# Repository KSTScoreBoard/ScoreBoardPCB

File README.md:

# ScoreBoardPCB

## メモ
LEDアノード側のダイオードの足間隔が狭い＆スルーホールが細い

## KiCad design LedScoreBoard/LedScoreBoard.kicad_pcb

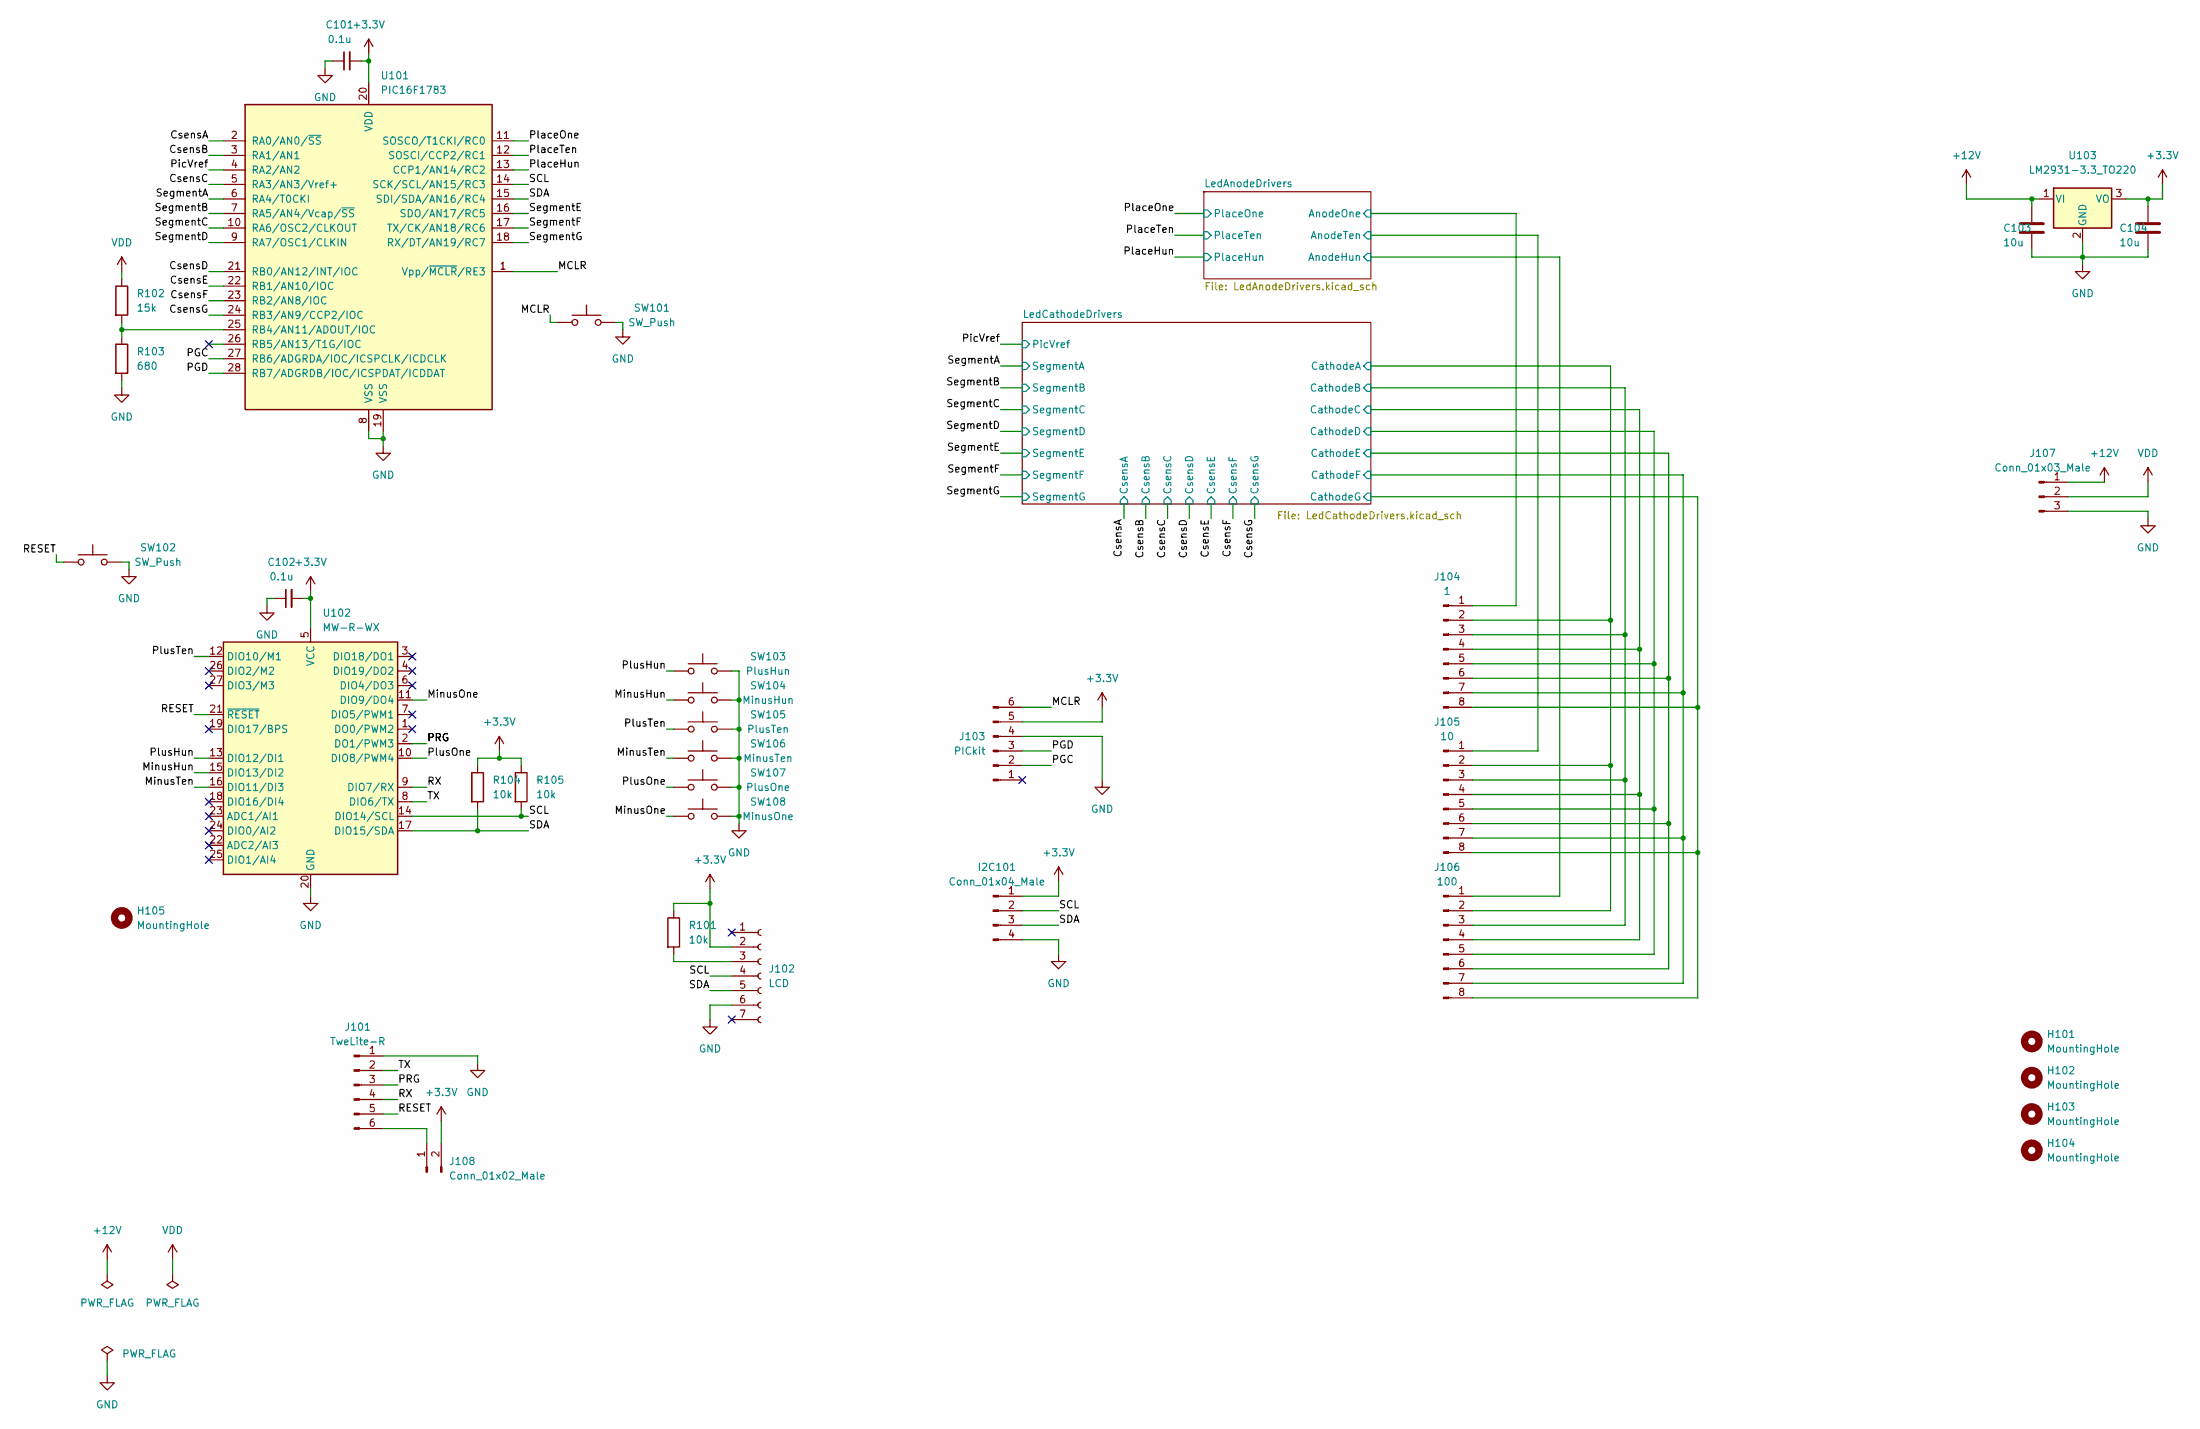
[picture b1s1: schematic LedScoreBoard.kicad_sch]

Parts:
C101, C102: 0.1u; C_0603_1608Metric
C103, C104: 10u; C_0603_1608Metric
H101, H102, H103, H104: MountingHole; MountingHole_3.2mm_M3
H105: MountingHole; MountingHole_6.4mm_M6
I2C101: Conn_01x04_Male; PinHeader_1x04_P2.54mm_Vertical
J101: TweLite-R; PinSocket_1x06_P2.54mm_Horizontal
J102: LCD; PinSocket_1x07_P2.54mm_Vertical
J103: PICkit; PinHeader_1x06_P2.54mm_Horizontal
J104: 1; JST_VH_B8P-VH_1x08_P3.96mm_Vertical
J105: 10; JST_VH_B8P-VH_1x08_P3.96mm_Vertical
J106: 100; JST_VH_B8P-VH_1x08_P3.96mm_Vertical
J107: Conn_01x03_Male; JST_VH_B3P-VH_1x03_P3.96mm_Vertical
J108: Conn_01x02_Male; PinHeader_1x02_P2.54mm_Vertical
R101, R104, R105: 10k; R_0603_1608Metric
R102: 15k; R_0603_1608Metric
R103: 680; R_0603_1608Metric
SW101, SW102: SW_Push; SW_PUSH_6mm
SW103: PlusHun; SW_PUSH_6mm
SW104: MinusHun; SW_PUSH_6mm
SW105: PlusTen; SW_PUSH_6mm
SW106: MinusTen; SW_PUSH_6mm
SW107: PlusOne; SW_PUSH_6mm
SW108: MinusOne; SW_PUSH_6mm
U101: PIC16F1783; DIP-28_W7.62mm_Socket_LongPads
U102: MW-R-WX; MonoWireless_TWE-L-WX
U103: LM2931-3.3_TO220; TO-220-3_Vertical

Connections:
+3.3V: C101.2, C102.2, C104.1, I2C101.1, J102.2, J103.5, J108.2, R101.1, R104.1, R105.1, U101.20 (VDD), U102.5 (VCC), U103.3 (VO)
+12V: C103.1, J107.1, U103.1 (VI); also elsewhere on the board
/CsensA: U101.2 (RA0/AN0/~SS); also elsewhere on the board
/CsensB: U101.3 (RA1/AN1); also elsewhere on the board
/CsensC: U101.5 (RA3/AN3/Vref+); also elsewhere on the board
/CsensD: U101.21 (RB0/AN12/INT/IOC); also elsewhere on the board
/CsensE: U101.22 (RB1/AN10/IOC); also elsewhere on the board
/CsensF: U101.23 (RB2/AN8/IOC); also elsewhere on the board
/CsensG: U101.24 (RB3/AN9/CCP2/IOC); also elsewhere on the board
/LedAnodeDrivers/AnodeHun: J106.1; also elsewhere on the board
/LedAnodeDrivers/AnodeOne: J104.1; also elsewhere on the board
/LedAnodeDrivers/AnodeTen: J105.1; also elsewhere on the board
/LedCathodeDrivers/CathodeA: J104.2, J105.2, J106.2; also elsewhere on the board
/LedCathodeDrivers/CathodeB: J104.3, J105.3, J106.3; also elsewhere on the board
/LedCathodeDrivers/CathodeC: J104.4, J105.4, J106.4; also elsewhere on the board
/LedCathodeDrivers/CathodeD: J104.5, J105.5, J106.5; also elsewhere on the board
/LedCathodeDrivers/CathodeE: J104.6, J105.6, J106.6; also elsewhere on the board
/LedCathodeDrivers/CathodeF: J104.7, J105.7, J106.7; also elsewhere on the board
/LedCathodeDrivers/CathodeG: J104.8, J105.8, J106.8; also elsewhere on the board
/MCLR: J103.6, SW101.1, U101.1 (Vpp/~MCLR/RE3)
/MinusHun: SW104.1, U102.15 (DIO13/DI2)
/MinusOne: SW108.1, U102.11 (DIO9/DO4)
/MinusTen: SW106.1, U102.16 (DIO11/DI3)
/PGC: J103.2, U101.27 (RB6/ADGRDA/IOC/ICSPCLK/ICDCLK)
/PGD: J103.3, U101.28 (RB7/ADGRDB/IOC/ICSPDAT/ICDDAT)
/PRG: J101.3, U102.2 (DO1/PWM3)
/PicVref: U101.4 (RA2/AN2); also elsewhere on the board
/PlaceHun: U101.13 (CCP1/AN14/RC2); also elsewhere on the board
/PlaceOne: U101.11 (SOSCO/T1CKI/RC0); also elsewhere on the board
/PlaceTen: U101.12 (SOSCI/CCP2/RC1); also elsewhere on the board
/PlusHun: SW103.1, U102.13 (DIO12/DI1)
/PlusOne: SW107.1, U102.10 (DIO8/PWM4)
/PlusTen: SW105.1, U102.12 (DIO10/M1)
/RESET: J101.5, SW102.1, U102.21 (~RESET)
/RX: J101.4, U102.9 (DIO7/RX)
/SCL: I2C101.2, J102.4, R105.2, U101.14 (SCK/SCL/AN15/RC3), U102.14 (DIO14/SCL)
/SDA: I2C101.3, J102.5, R104.2, U101.15 (SDI/SDA/AN16/RC4), U102.17 (DIO15/SDA)
/SegmentA: U101.6 (RA4/T0CKI); also elsewhere on the board
/SegmentB: U101.7 (RA5/AN4/Vcap/~SS); also elsewhere on the board
/SegmentC: U101.10 (RA6/OSC2/CLKOUT); also elsewhere on the board
/SegmentD: U101.9 (RA7/OSC1/CLKIN); also elsewhere on the board
/SegmentE: U101.16 (SDO/AN17/RC5); also elsewhere on the board
/SegmentF: U101.17 (TX/CK/AN18/RC6); also elsewhere on the board
/SegmentG: U101.18 (RX/DT/AN19/RC7); also elsewhere on the board
/TX: J101.2, U102.8 (DIO6/TX)
GND: C101.1, C102.1, C103.2, C104.2, I2C101.4, J101.1, J102.6, J103.4, J107.3, R103.2, SW101.2, SW102.2, SW103.2, SW104.2, SW105.2, SW106.2, SW107.2, SW108.2, U101.8 (VSS), U101.19 (VSS), U102.20 (GND), U102.28 (GND), U102.30 (GND), U102.31 (GND), U102.32 (GND), U103.2 (GND); also elsewhere on the board
unnamed: J101.6, J108.1
unnamed: J102.3, R101.2
unnamed: R102.2, R103.1, U101.25 (RB4/AN11/ADOUT/IOC)
VDD: J107.2, R102.1; also elsewhere on the board

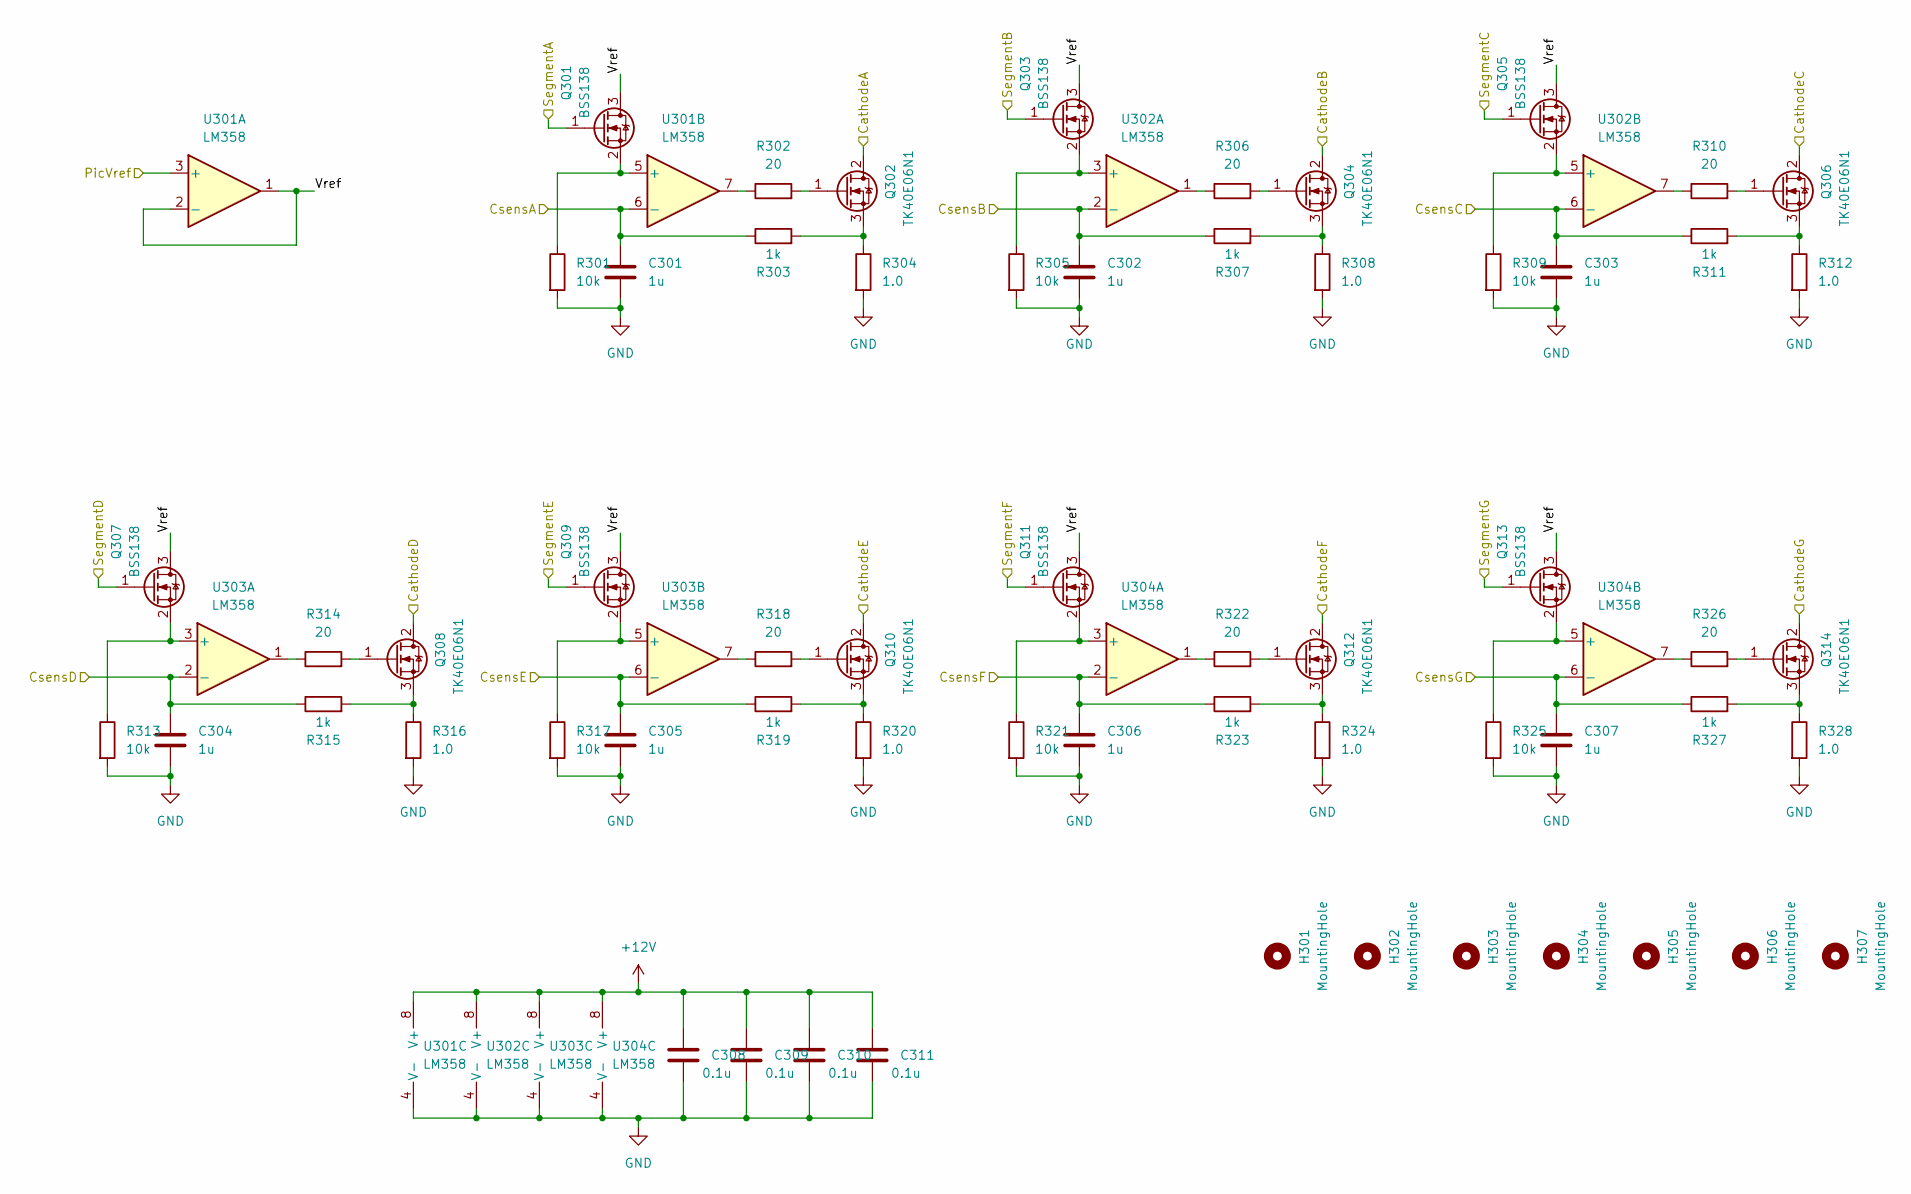
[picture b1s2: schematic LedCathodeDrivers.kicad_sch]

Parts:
C301, C302, C303, C304, C305, C306, C307: 1u; C_0603_1608Metric
C308, C309, C310, C311: 0.1u; C_0603_1608Metric
H301, H302, H303, H304, H305, H306, H307: MountingHole; MountingHole_2.2mm_M2
Q301, Q303, Q305, Q307, Q309, Q311, Q313: BSS138; SOT-23_Handsoldering
Q302, Q304, Q306, Q308, Q310, Q312, Q314: TK40E06N1; TO-220-3_Vertical
R301, R305, R309, R313, R317, R321, R325: 10k; R_0603_1608Metric
R302, R306, R310, R314, R318, R322, R326: 20; R_0603_1608Metric
R303, R307, R311, R315, R319, R323, R327: 1k; R_0603_1608Metric
R304, R308, R312, R316, R320, R324, R328: 1.0; R_2512_6332Metric_Pad1.40x3.35mm_HandSolder
U301, U302, U303, U304: LM358; SOP-8_3.9x4.9mm_P1.27mm

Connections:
+12V: C308.1, C309.1, C310.1, C311.1, U301.8 (V+), U302.8 (V+), U303.8 (V+), U304.8 (V+); also elsewhere on the board
/CsensA: C301.1, R303.1, U301.6 (-); also elsewhere on the board
/CsensB: C302.1, R307.1, U302.2 (-); also elsewhere on the board
/CsensC: C303.1, R311.1, U302.6 (-); also elsewhere on the board
/CsensD: C304.1, R315.1, U303.2 (-); also elsewhere on the board
/CsensE: C305.1, R319.1, U303.6 (-); also elsewhere on the board
/CsensF: C306.1, R323.1, U304.2 (-); also elsewhere on the board
/CsensG: C307.1, R327.1, U304.6 (-); also elsewhere on the board
/LedCathodeDrivers/CathodeA: Q302.2 (D); also elsewhere on the board
/LedCathodeDrivers/CathodeB: Q304.2 (D); also elsewhere on the board
/LedCathodeDrivers/CathodeC: Q306.2 (D); also elsewhere on the board
/LedCathodeDrivers/CathodeD: Q308.2 (D); also elsewhere on the board
/LedCathodeDrivers/CathodeE: Q310.2 (D); also elsewhere on the board
/LedCathodeDrivers/CathodeF: Q312.2 (D); also elsewhere on the board
/LedCathodeDrivers/CathodeG: Q314.2 (D); also elsewhere on the board
/LedCathodeDrivers/Vref: Q301.3 (D), Q303.3 (D), Q305.3 (D), Q307.3 (D), Q309.3 (D), Q311.3 (D), Q313.3 (D), U301.1, U301.2 (-)
/PicVref: U301.3 (+); also elsewhere on the board
/SegmentA: Q301.1 (G); also elsewhere on the board
/SegmentB: Q303.1 (G); also elsewhere on the board
/SegmentC: Q305.1 (G); also elsewhere on the board
/SegmentD: Q307.1 (G); also elsewhere on the board
/SegmentE: Q309.1 (G); also elsewhere on the board
/SegmentF: Q311.1 (G); also elsewhere on the board
/SegmentG: Q313.1 (G); also elsewhere on the board
GND: C301.2, C302.2, C303.2, C304.2, C305.2, C306.2, C307.2, C308.2, C309.2, C310.2, C311.2, R301.2, R304.2, R305.2, R308.2, R309.2, R312.2, R313.2, R316.2, R317.2, R320.2, R321.2, R324.2, R325.2, R328.2, U301.4 (V-), U302.4 (V-), U303.4 (V-), U304.4 (V-); also elsewhere on the board
unnamed: Q301.2 (S), R301.1, U301.5 (+)
unnamed: Q302.1 (G), R302.2
unnamed: Q302.3 (S), R303.2, R304.1
unnamed: Q303.2 (S), R305.1, U302.3 (+)
unnamed: Q304.1 (G), R306.2
unnamed: Q304.3 (S), R307.2, R308.1
unnamed: Q305.2 (S), R309.1, U302.5 (+)
unnamed: Q306.1 (G), R310.2
unnamed: Q306.3 (S), R311.2, R312.1
unnamed: Q307.2 (S), R313.1, U303.3 (+)
unnamed: Q308.1 (G), R314.2
unnamed: Q308.3 (S), R315.2, R316.1
unnamed: Q309.2 (S), R317.1, U303.5 (+)
unnamed: Q310.1 (G), R318.2
unnamed: Q310.3 (S), R319.2, R320.1
unnamed: Q311.2 (S), R321.1, U304.3 (+)
unnamed: Q312.1 (G), R322.2
unnamed: Q312.3 (S), R323.2, R324.1
unnamed: Q313.2 (S), R325.1, U304.5 (+)
unnamed: Q314.1 (G), R326.2
unnamed: Q314.3 (S), R327.2, R328.1
unnamed: R302.1, U301.7
unnamed: R306.1, U302.1
unnamed: R310.1, U302.7
unnamed: R314.1, U303.1
unnamed: R318.1, U303.7
unnamed: R322.1, U304.1
unnamed: R326.1, U304.7

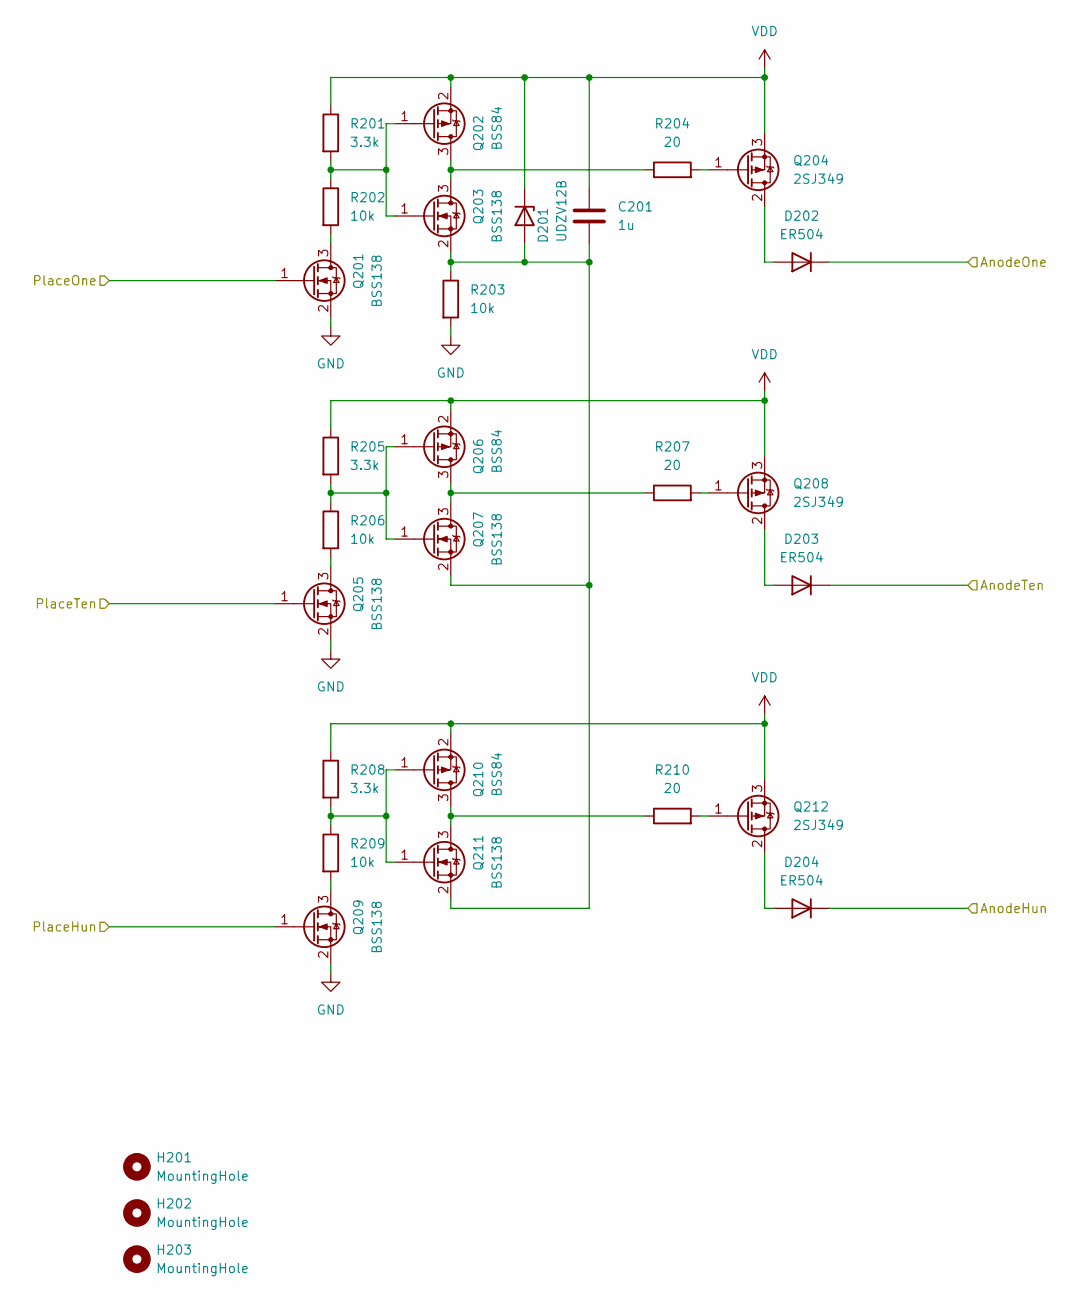
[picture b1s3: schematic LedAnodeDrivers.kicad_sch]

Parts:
C201: 1u; C_0603_1608Metric
D201: UDZV12B; D_TUMD2
D202, D203, D204: ER504; D_DO-27_P15.24mm_Horizontal
H201, H202, H203: MountingHole; MountingHole_2.2mm_M2
Q201, Q203, Q205, Q207, Q209, Q211: BSS138; SOT-23_Handsoldering
Q202, Q206, Q210: BSS84; SOT-23_Handsoldering
Q204, Q208, Q212: 2SJ349; TO-220-3_Vertical
R201, R205, R208: 3.3k; R_0603_1608Metric
R202, R203, R206, R209: 10k; R_0603_1608Metric
R204, R207, R210: 20; R_0603_1608Metric

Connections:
/LedAnodeDrivers/AnodeHun: D204.1 (K); also elsewhere on the board
/LedAnodeDrivers/AnodeOne: D202.1 (K); also elsewhere on the board
/LedAnodeDrivers/AnodeTen: D203.1 (K); also elsewhere on the board
/PlaceHun: Q209.1 (G); also elsewhere on the board
/PlaceOne: Q201.1 (G); also elsewhere on the board
/PlaceTen: Q205.1 (G); also elsewhere on the board
GND: Q201.2 (S), Q205.2 (S), Q209.2 (S), R203.2; also elsewhere on the board
unnamed: C201.2, D201.2 (A), Q203.2 (S), Q207.2 (S), Q211.2 (S), R203.1
unnamed: D202.2 (A), Q204.2 (D)
unnamed: D203.2 (A), Q208.2 (D)
unnamed: D204.2 (A), Q212.2 (D)
unnamed: Q201.3 (D), R202.2
unnamed: Q202.1 (G), Q203.1 (G), R201.2, R202.1
unnamed: Q202.3 (D), Q203.3 (D), R204.1
unnamed: Q204.1 (G), R204.2
unnamed: Q205.3 (D), R206.2
unnamed: Q206.1 (G), Q207.1 (G), R205.2, R206.1
unnamed: Q206.3 (D), Q207.3 (D), R207.1
unnamed: Q208.1 (G), R207.2
unnamed: Q209.3 (D), R209.2
unnamed: Q210.1 (G), Q211.1 (G), R208.2, R209.1
unnamed: Q210.3 (D), Q211.3 (D), R210.1
unnamed: Q212.1 (G), R210.2
VDD: C201.1, D201.1 (K), Q202.2 (S), Q204.3 (S), Q206.2 (S), Q208.3 (S), Q210.2 (S), Q212.3 (S), R201.1, R205.1, R208.1; also elsewhere on the board

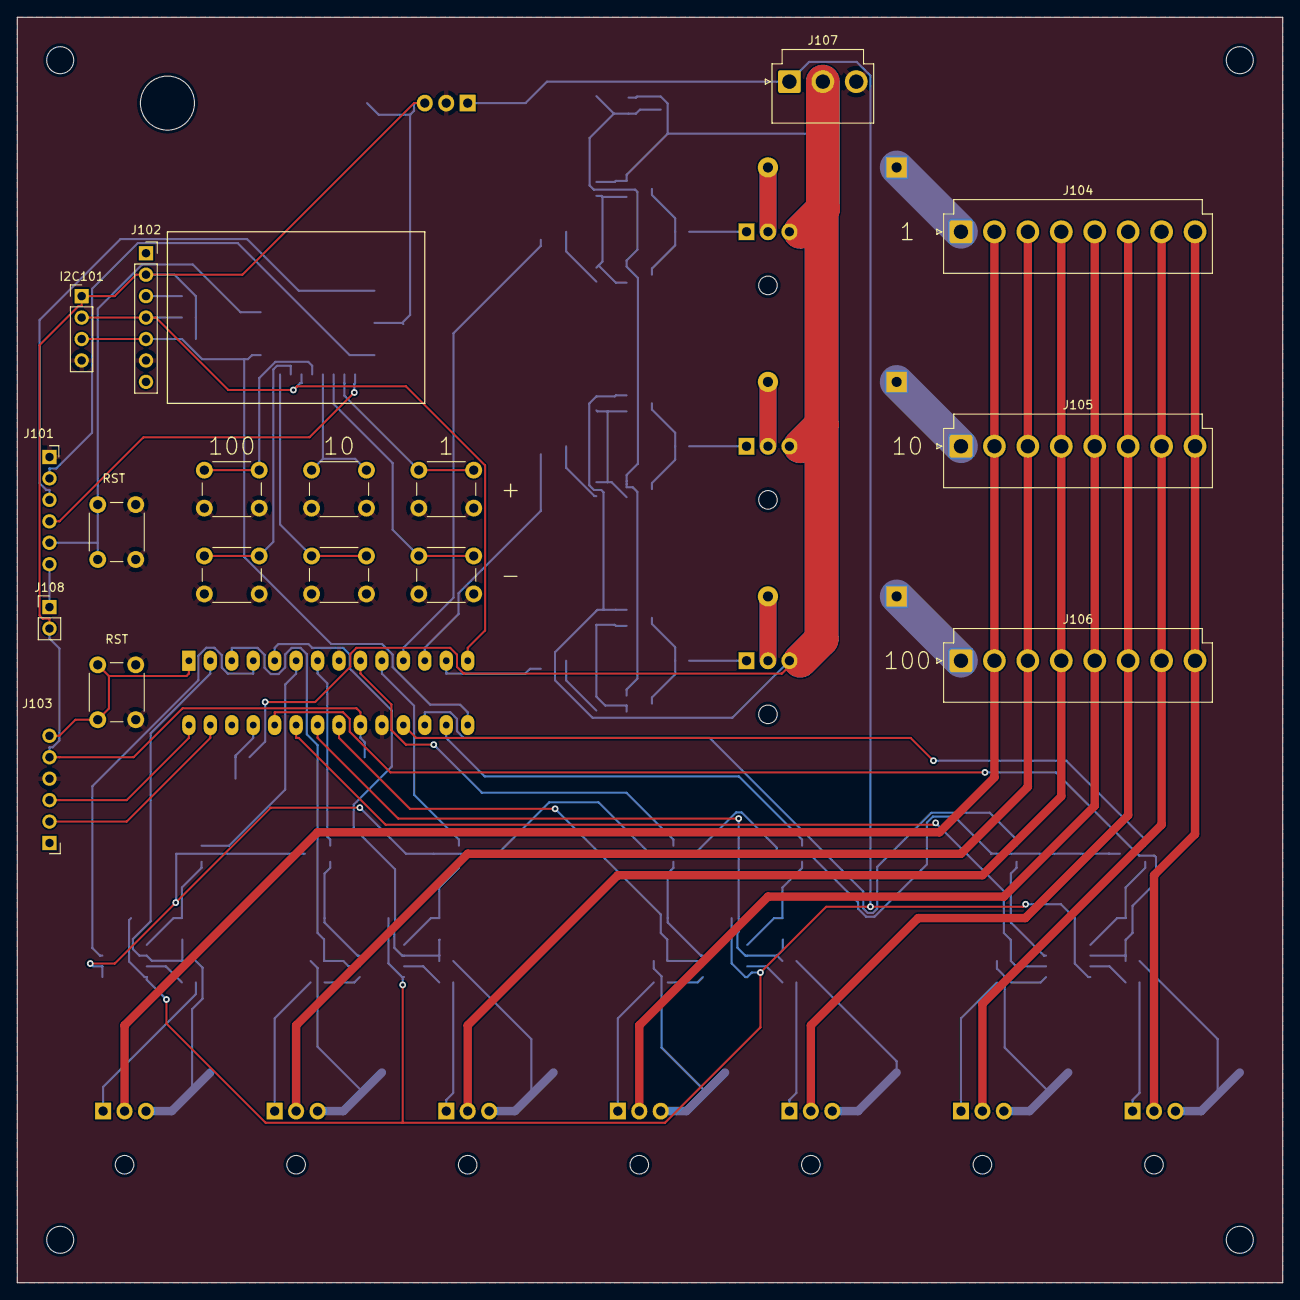
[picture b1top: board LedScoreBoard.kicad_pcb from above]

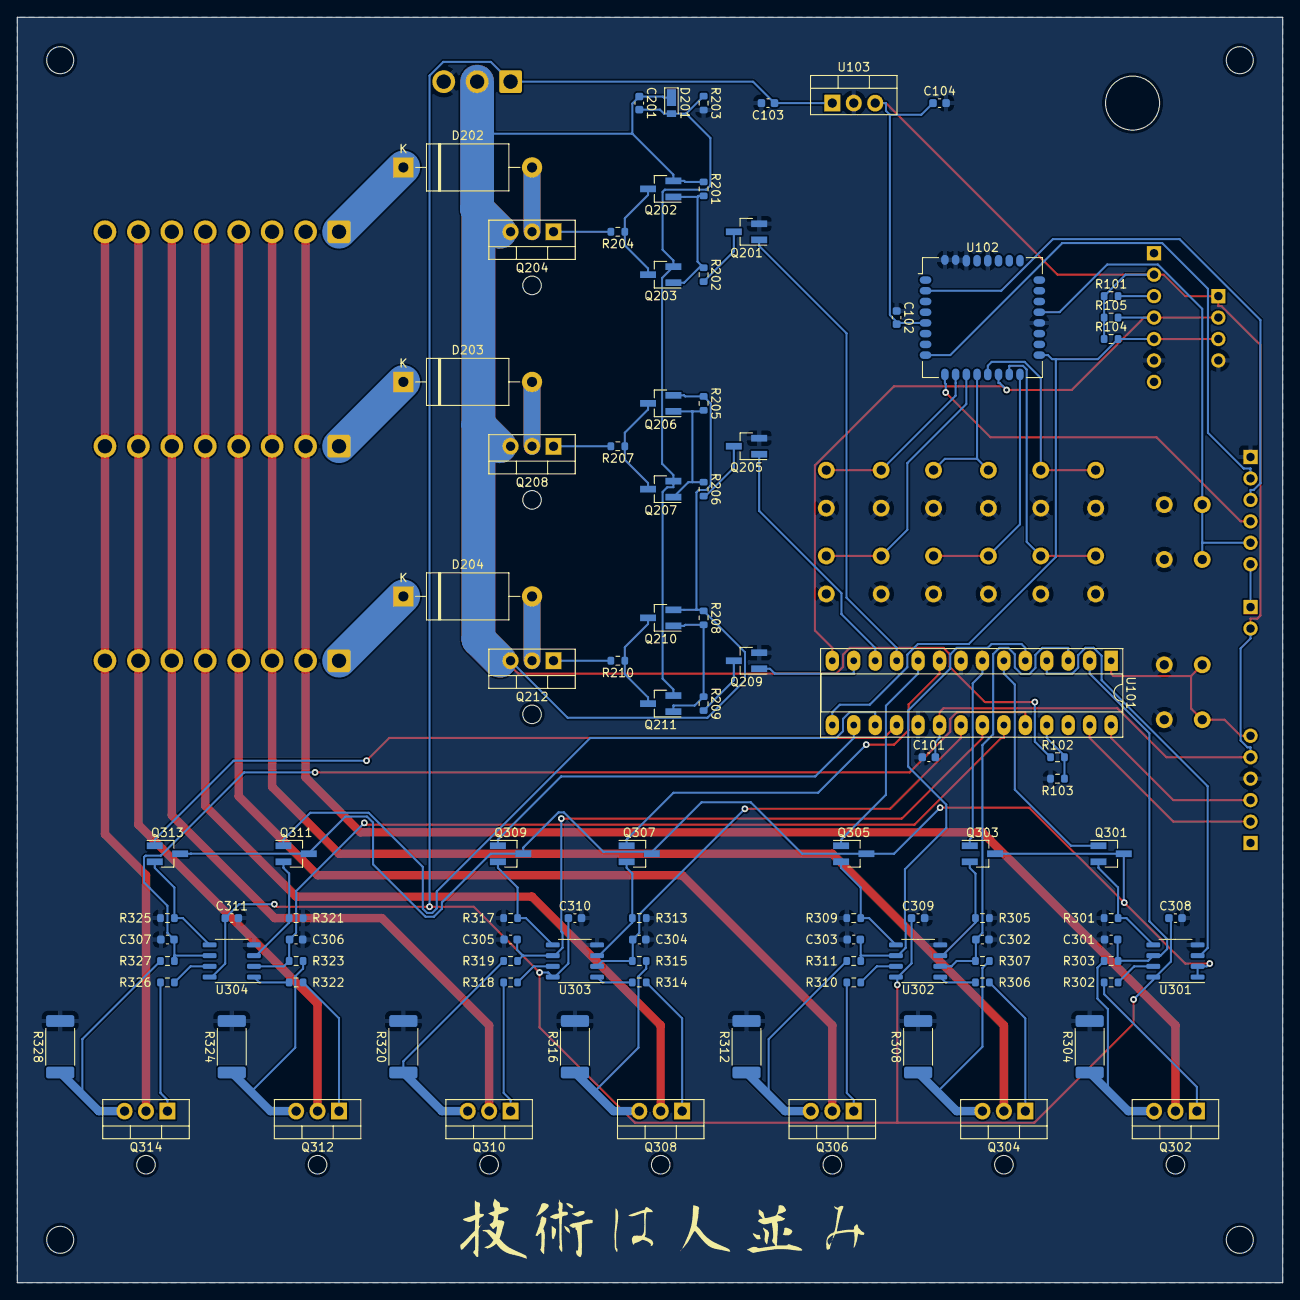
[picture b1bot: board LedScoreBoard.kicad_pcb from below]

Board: 2 copper layers, 149.9 x 149.9 mm, 128 parts (96 on the bottom side), 95 nets.

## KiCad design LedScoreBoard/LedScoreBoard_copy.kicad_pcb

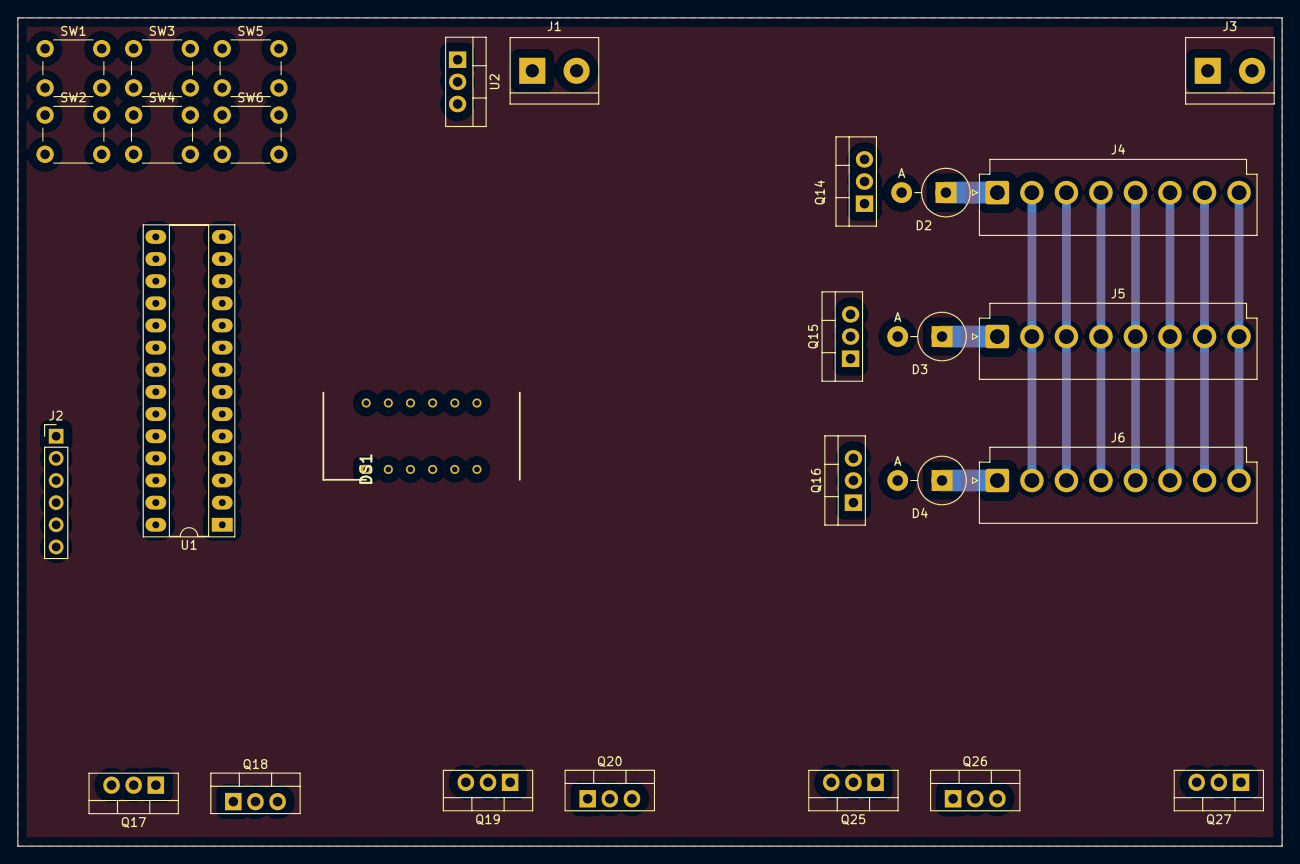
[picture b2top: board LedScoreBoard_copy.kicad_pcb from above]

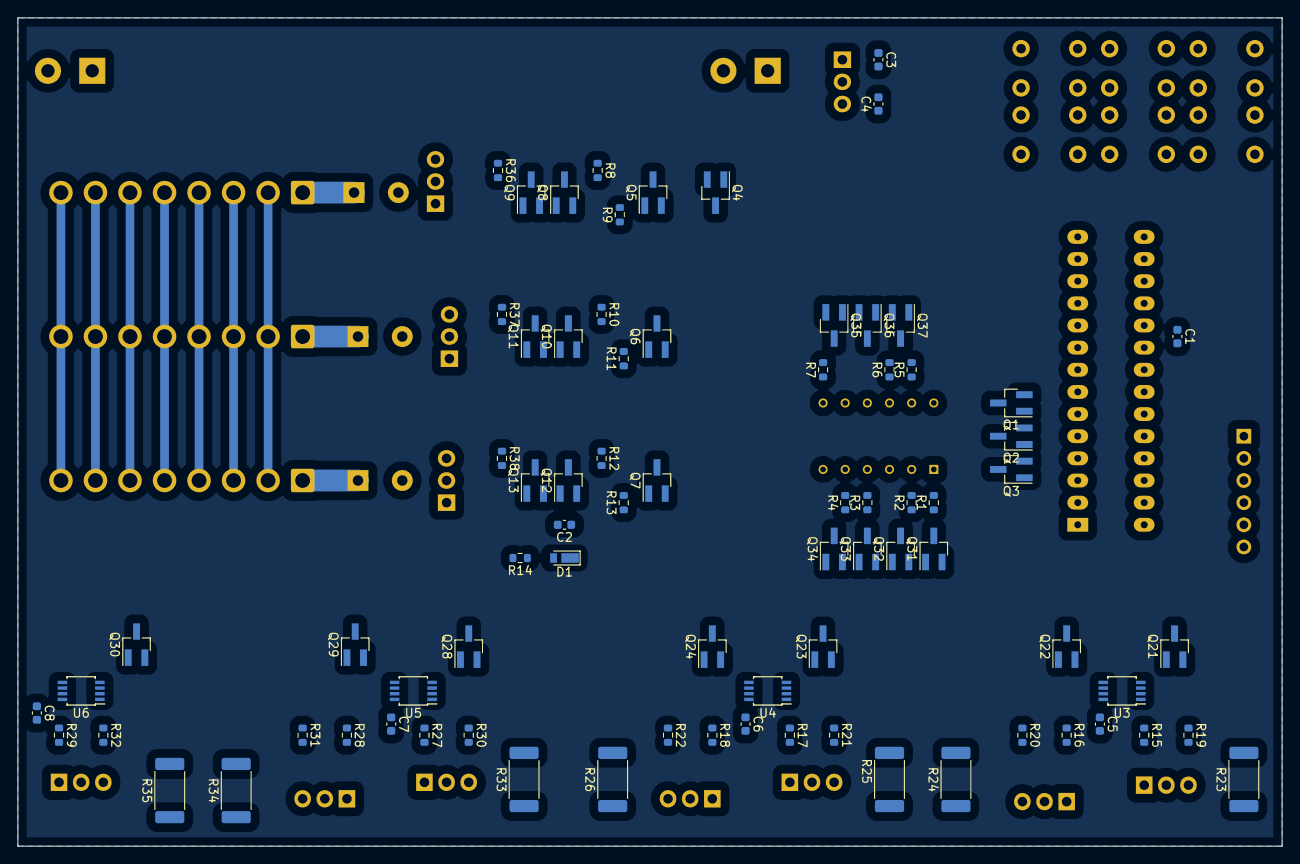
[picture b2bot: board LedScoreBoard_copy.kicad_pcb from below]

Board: 2 copper layers, 145.0 x 95.0 mm, 106 parts (78 on the bottom side), 104 nets.

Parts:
C1, C5, C6, C7, C8: 0.1u; C_0603_1608Metric
C2: 1u; C_0603_1608Metric
C3, C4: 10u; C_0603_1608Metric
D1: GDZJ112C; D_TUMD2
D2, D3, D4: ER504; D_DO-27_P5.08mm_Vertical_AnodeUp
DS1: 2831BS-RIGHT-ANGLE; DIPS762W45P254L2253H610Q12N
J1, J3: Conn_01x02_Male; TerminalBlock_bornier-2_P5.08mm
J2: Conn_01x06_Male; PinHeader_1x06_P2.54mm_Vertical
J4, J5, J6: Conn_01x08_Male; JST_VH_B8P-VH_1x08_P3.96mm_Vertical
Q1, Q2, Q3, Q8, Q10, Q12: BSS84; SOT-23_Handsoldering
Q4, Q5, Q6, Q7, Q9, Q11, Q13, Q21, Q22, Q23, Q24, Q28, Q29, Q30, Q31, Q32, Q33, Q34, Q35, Q36, Q37: BSS138; SOT-23_Handsoldering
Q14, Q15, Q16: 2SJ349; TO-220-3_Vertical
Q17, Q18, Q19, Q20, Q25, Q26, Q27: TK40E06N1; TO-220-3_Vertical
R1, R2, R3, R4, R5, R6, R7, R19, R20, R21, R22, R30, R31, R32: 1k; R_0603_1608Metric
R8, R10, R12: 3.3k; R_0603_1608Metric
R9, R11, R13, R14: 10k; R_0603_1608Metric
R15, R16, R17, R18, R27, R28, R29, R36, R37, R38: 20; R_0603_1608Metric
R23, R24, R25, R26, R33, R34, R35: 1.0; R_2512_6332Metric_Pad1.40x3.35mm_HandSolder
SW1, SW2, SW3, SW4, SW5, SW6: SW_Push; SW_PUSH_6mm
U1: PIC16F1516-ISP; DIP-28_W7.62mm_Socket_LongPads
U2: LM2931-3.3_TO220; TO-220-3_Vertical
U3, U4, U5, U6: LM358; TSSOP-8_3x3mm_P0.65mm

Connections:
+3.3V: C1.2, C4.1, J2.2, Q1.2 (S), Q2.2 (S), Q3.2 (S), U1.20 (VDD), U2.3 (VO)
+12V: C3.1, C5.1, C6.1, C7.1, C8.1, J1.1, U2.1 (VI), U3.8 (V+), U4.8 (V+), U5.8 (V+), U6.8 (V+)
/MCLR: J2.1, U1.1 (Vpp/~MCLR/RE3)
/PGC: J2.5, U1.28 (RB7/ADGRDB/IOC/ICSPDAT/ICDDAT)
/PGD: J2.4, U1.27 (RB6/ADGRDA/IOC/ICSPCLK/ICDCLK)
/Vref: Q21.3 (D), Q22.3 (D), Q23.3 (D), Q24.3 (D), Q28.3 (D), Q29.3 (D), Q30.3 (D)
/anodeHun: D4.1 (K), J6.1
/anodeOne: D2.1 (K), J4.1
/anodeTen: D3.1 (K), J5.1
/cathodeA: J4.2, J5.2, J6.2, Q17.2 (D)
/cathodeB: J4.3, J5.3, J6.3, Q18.2 (D)
/cathodeC: J4.4, J5.4, J6.4, Q19.2 (D)
/cathodeD: J4.5, J5.5, J6.5, Q20.2 (D)
/cathodeE: J4.6, J5.6, J6.6, Q25.2 (D)
/cathodeF: J4.7, J5.7, J6.7, Q26.2 (D)
/cathodeG: J4.8, J5.8, J6.8, Q27.2 (D)
/enable: Q4.1 (G), U1.9 (RA7/OSC1/CLKIN)
/minusHun: SW2.1, U1.26 (RB5/AN13/T1G/IOC)
/minusOne: SW6.1, U1.22 (RB1/AN10/IOC)
/minusTen: SW4.1, U1.24 (RB3/AN9/CCP2/IOC)
/placeHun: Q1.1 (G), Q7.1 (G), U1.13 (CCP1/AN14/RC2)
/placeOne: Q3.1 (G), Q5.1 (G), U1.11 (SOSCO/T1CKI/RC0)
/placeTen: Q2.1 (G), Q6.1 (G), U1.12 (SOSCI/CCP2/RC1)
/plusHun: SW1.1, U1.25 (RB4/AN11/ADOUT/IOC)
/plusOne: SW5.1, U1.21 (RB0/AN12/INT/IOC)
/plusTen: SW3.1, U1.23 (RB2/AN8/IOC)
/segmentA: Q21.1 (G), Q24.1 (G), Q37.1 (G), U1.2 (RA0/AN0/~SS)
/segmentB: Q22.1 (G), Q35.1 (G), U1.3 (RA1/AN1)
/segmentC: Q33.1 (G), U1.4 (RA2/AN2)
/segmentD: Q23.1 (G), Q32.1 (G), U1.5 (RA3/AN3/Vref+)
/segmentE: Q28.1 (G), Q31.1 (G), U1.6 (RA4/T0CKI)
/segmentF: Q29.1 (G), Q36.1 (G), U1.7 (RA5/AN4/Vcap/~SS)
/segmentG: Q30.1 (G), Q34.1 (G), U1.10 (RA6/OSC2/CLKOUT)
GND: C1.1, C3.2, C4.2, C5.2, C6.2, C7.2, C8.2, J1.2, J2.3, J3.2, Q4.2 (S), Q31.2 (S), Q32.2 (S), Q33.2 (S), Q34.2 (S), Q35.2 (S), Q36.2 (S), Q37.2 (S), R14.2, R23.2, R24.2, R25.2, R26.2, R33.2, R34.2, R35.2, SW1.2, SW2.2, SW3.2, SW4.2, SW5.2, SW6.2, U1.8 (VSS), U1.19 (VSS), U2.2 (GND), U3.4 (V-), U4.4 (V-), U5.4 (V-), U6.4 (V-)
unnamed: C2.2, D1.2 (A), Q9.2 (S), Q11.2 (S), Q13.2 (S), R14.1
unnamed: D2.2 (A), Q14.2 (D)
unnamed: D3.2 (A), Q15.2 (D)
unnamed: D4.2 (A), Q16.2 (D)
unnamed: DS1.1 (CATHODE_E), R1.2
unnamed: DS1.2 (CATHODE_D), R2.2
unnamed: DS1.4 (CATHODE_C), R3.2
unnamed: DS1.5 (CATHODE_G), R4.2
unnamed: DS1.7 (CATHODE_B), R7.1
unnamed: DS1.8 (COMMON_ANODE_DIG_3), Q3.3 (D)
unnamed: DS1.9 (COMMON_ANODE_DIG_2), Q2.3 (D)
unnamed: DS1.10 (CATHODE_F), R6.1
unnamed: DS1.11 (CATHODE_A), R5.1
unnamed: DS1.12 (COMMON_ANODE_DIG_1), Q1.3 (D)
unnamed: Q4.3 (D), Q5.2 (S), Q6.2 (S), Q7.2 (S)
unnamed: Q5.3 (D), R9.2
unnamed: Q6.3 (D), R11.2
unnamed: Q7.3 (D), R13.2
unnamed: Q8.1 (G), Q9.1 (G), R8.2, R9.1
unnamed: Q8.3 (D), Q9.3 (D), R36.1
unnamed: Q10.1 (G), Q11.1 (G), R10.2, R11.1
unnamed: Q10.3 (D), Q11.3 (D), R37.1
unnamed: Q12.1 (G), Q13.1 (G), R12.2, R13.1
unnamed: Q12.3 (D), Q13.3 (D), R38.1
unnamed: Q14.1 (G), R36.2
unnamed: Q15.1 (G), R37.2
unnamed: Q16.1 (G), R38.2
unnamed: Q17.1 (G), R15.2
unnamed: Q17.3 (S), R19.2, R23.1
unnamed: Q18.1 (G), R16.2
unnamed: Q18.3 (S), R20.2, R24.1
unnamed: Q19.1 (G), R17.2
unnamed: Q19.3 (S), R21.2, R25.1
unnamed: Q20.1 (G), R18.2
unnamed: Q20.3 (S), R22.2, R26.1
unnamed: Q21.2 (S), U3.3 (+)
unnamed: Q22.2 (S), U3.5 (+)
unnamed: Q23.2 (S), U4.3 (+)
unnamed: Q24.2 (S), U4.5 (+)
unnamed: Q25.1 (G), R27.2
unnamed: Q25.3 (S), R30.2, R33.1
unnamed: Q26.1 (G), R28.2
unnamed: Q26.3 (S), R31.2, R34.1
unnamed: Q27.1 (G), R29.2
unnamed: Q27.3 (S), R32.2, R35.1
unnamed: Q28.2 (S), U5.3 (+)
unnamed: Q29.2 (S), U5.5 (+)
unnamed: Q30.2 (S), U6.3 (+)
unnamed: Q31.3 (D), R1.1
unnamed: Q32.3 (D), R2.1
unnamed: Q33.3 (D), R3.1
unnamed: Q34.3 (D), R4.1
unnamed: Q35.3 (D), R7.2
unnamed: Q36.3 (D), R6.2
unnamed: Q37.3 (D), R5.2
unnamed: R15.1, U3.1
unnamed: R16.1, U3.7
unnamed: R17.1, U4.1
unnamed: R18.1, U4.7
unnamed: R19.1, U3.2 (-)
unnamed: R20.1, U3.6 (-)
unnamed: R21.1, U4.2 (-)
unnamed: R22.1, U4.6 (-)
unnamed: R27.1, U5.1
unnamed: R28.1, U5.7
unnamed: R29.1, U6.1
unnamed: R30.1, U5.2 (-)
unnamed: R31.1, U5.6 (-)
unnamed: R32.1, U6.2 (-)
VDD: C2.1, D1.1 (K), J3.1, Q8.2 (S), Q10.2 (S), Q12.2 (S), Q14.3 (S), Q15.3 (S), Q16.3 (S), R8.1, R10.1, R12.1

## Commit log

2022-09-24 基本設計
2022-10-01 SerialTerminal
2022-10-08 TweLiteプロジェクト追加
2022-10-08 index移動
2022-10-08 TweLite内蔵型に変更
2022-10-09 回路図更新
2022-10-09 TweLiteアンテナフットプリント追加
2022-10-10 配置ブロック決定
2022-10-15 パターン完成
2022-10-16 アンテナ穴径修正
2022-10-16 シルク追加
2022-10-16 ヒートシンク穴追加
2022-10-19 Tweliteプログラム移動
2022-10-19 make gaber
2022-11-03 PIC/Twelite書き込み端子ネットリスト修正
2022-11-04 Vref修正
2022-11-06 回路修正
2022-11-08 ver2完成
